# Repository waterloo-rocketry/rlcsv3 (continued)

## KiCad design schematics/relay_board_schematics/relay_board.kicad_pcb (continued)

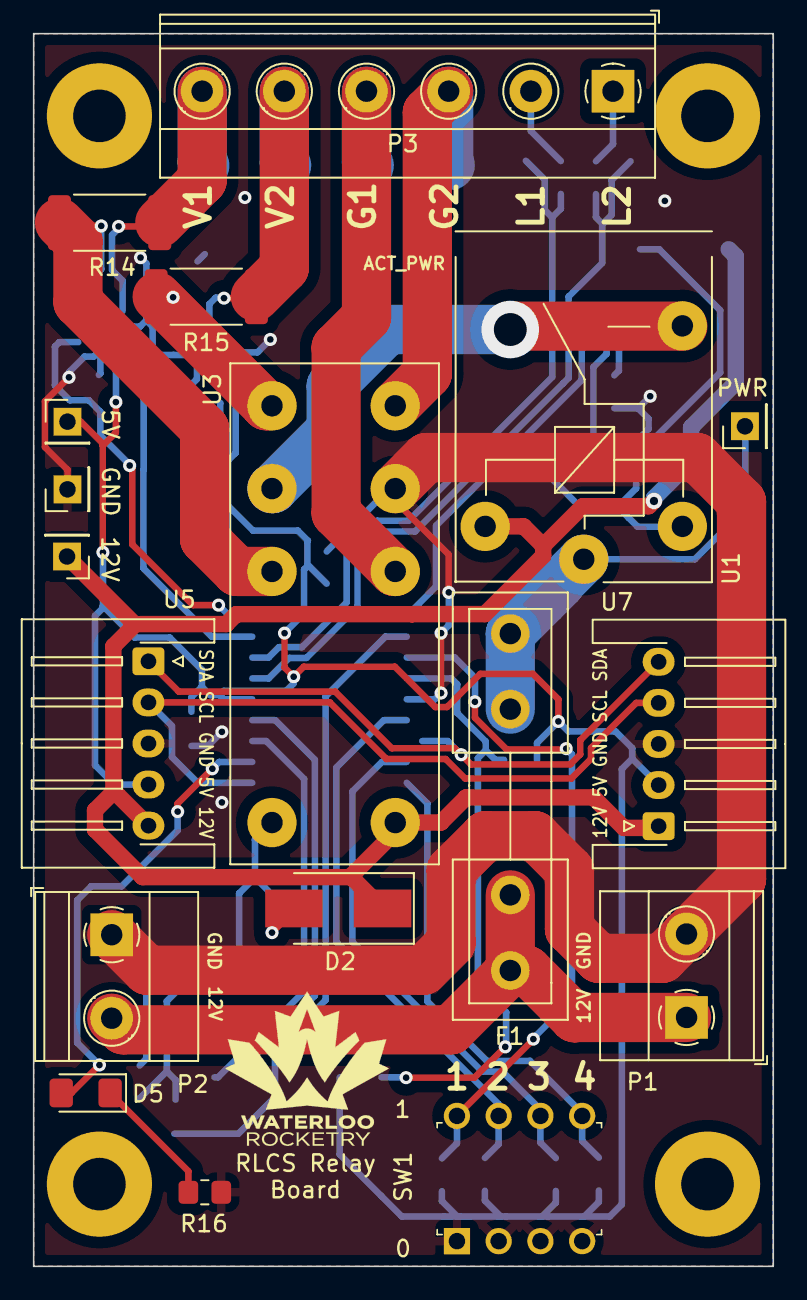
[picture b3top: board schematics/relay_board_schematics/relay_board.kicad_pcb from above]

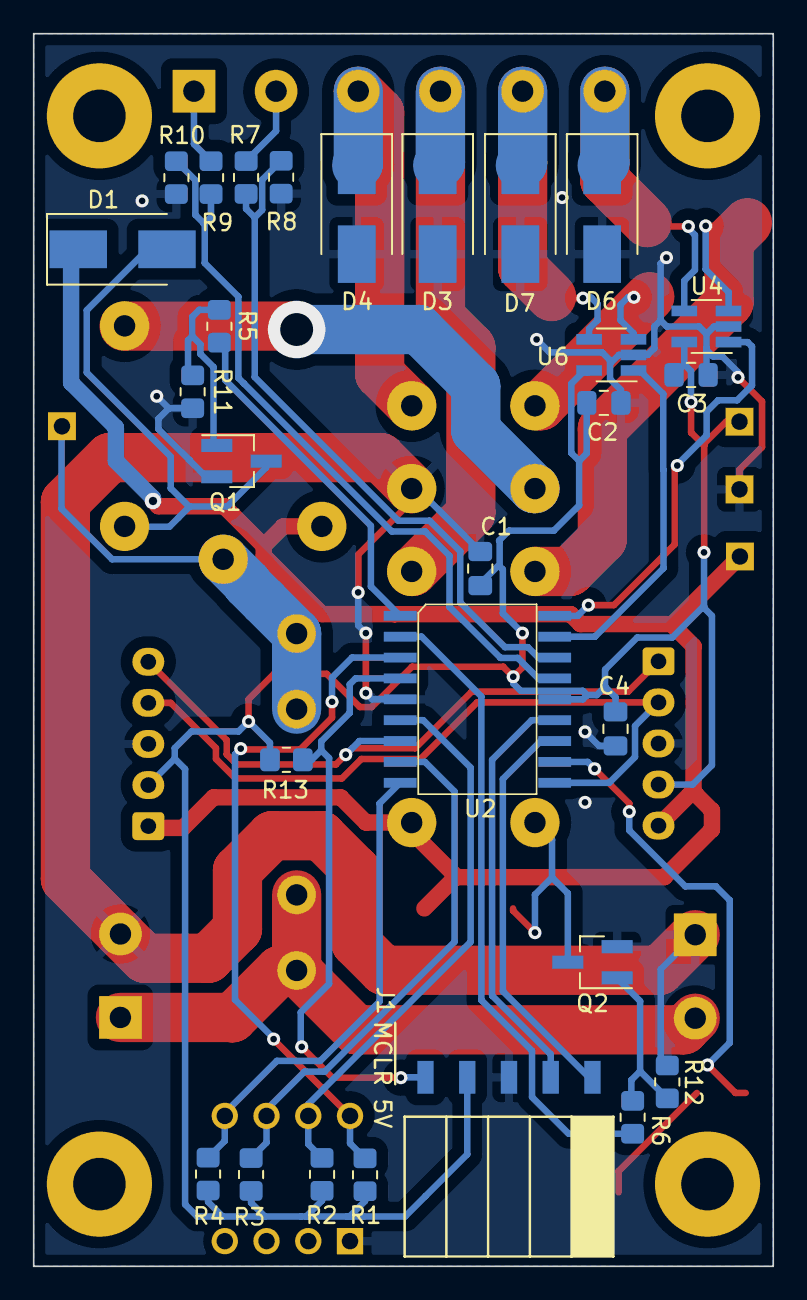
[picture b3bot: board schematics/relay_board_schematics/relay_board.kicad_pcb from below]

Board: 2 copper layers, 45.0 x 75.0 mm, 46 parts (28 on the bottom side), 35 nets.

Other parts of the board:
C4: 0.1uF; C_0805_2012Metric_Pad1.18x1.45mm_HandSolder

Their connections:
+5V: C4.2; also elsewhere on the board
GND: C4.1; also elsewhere on the board

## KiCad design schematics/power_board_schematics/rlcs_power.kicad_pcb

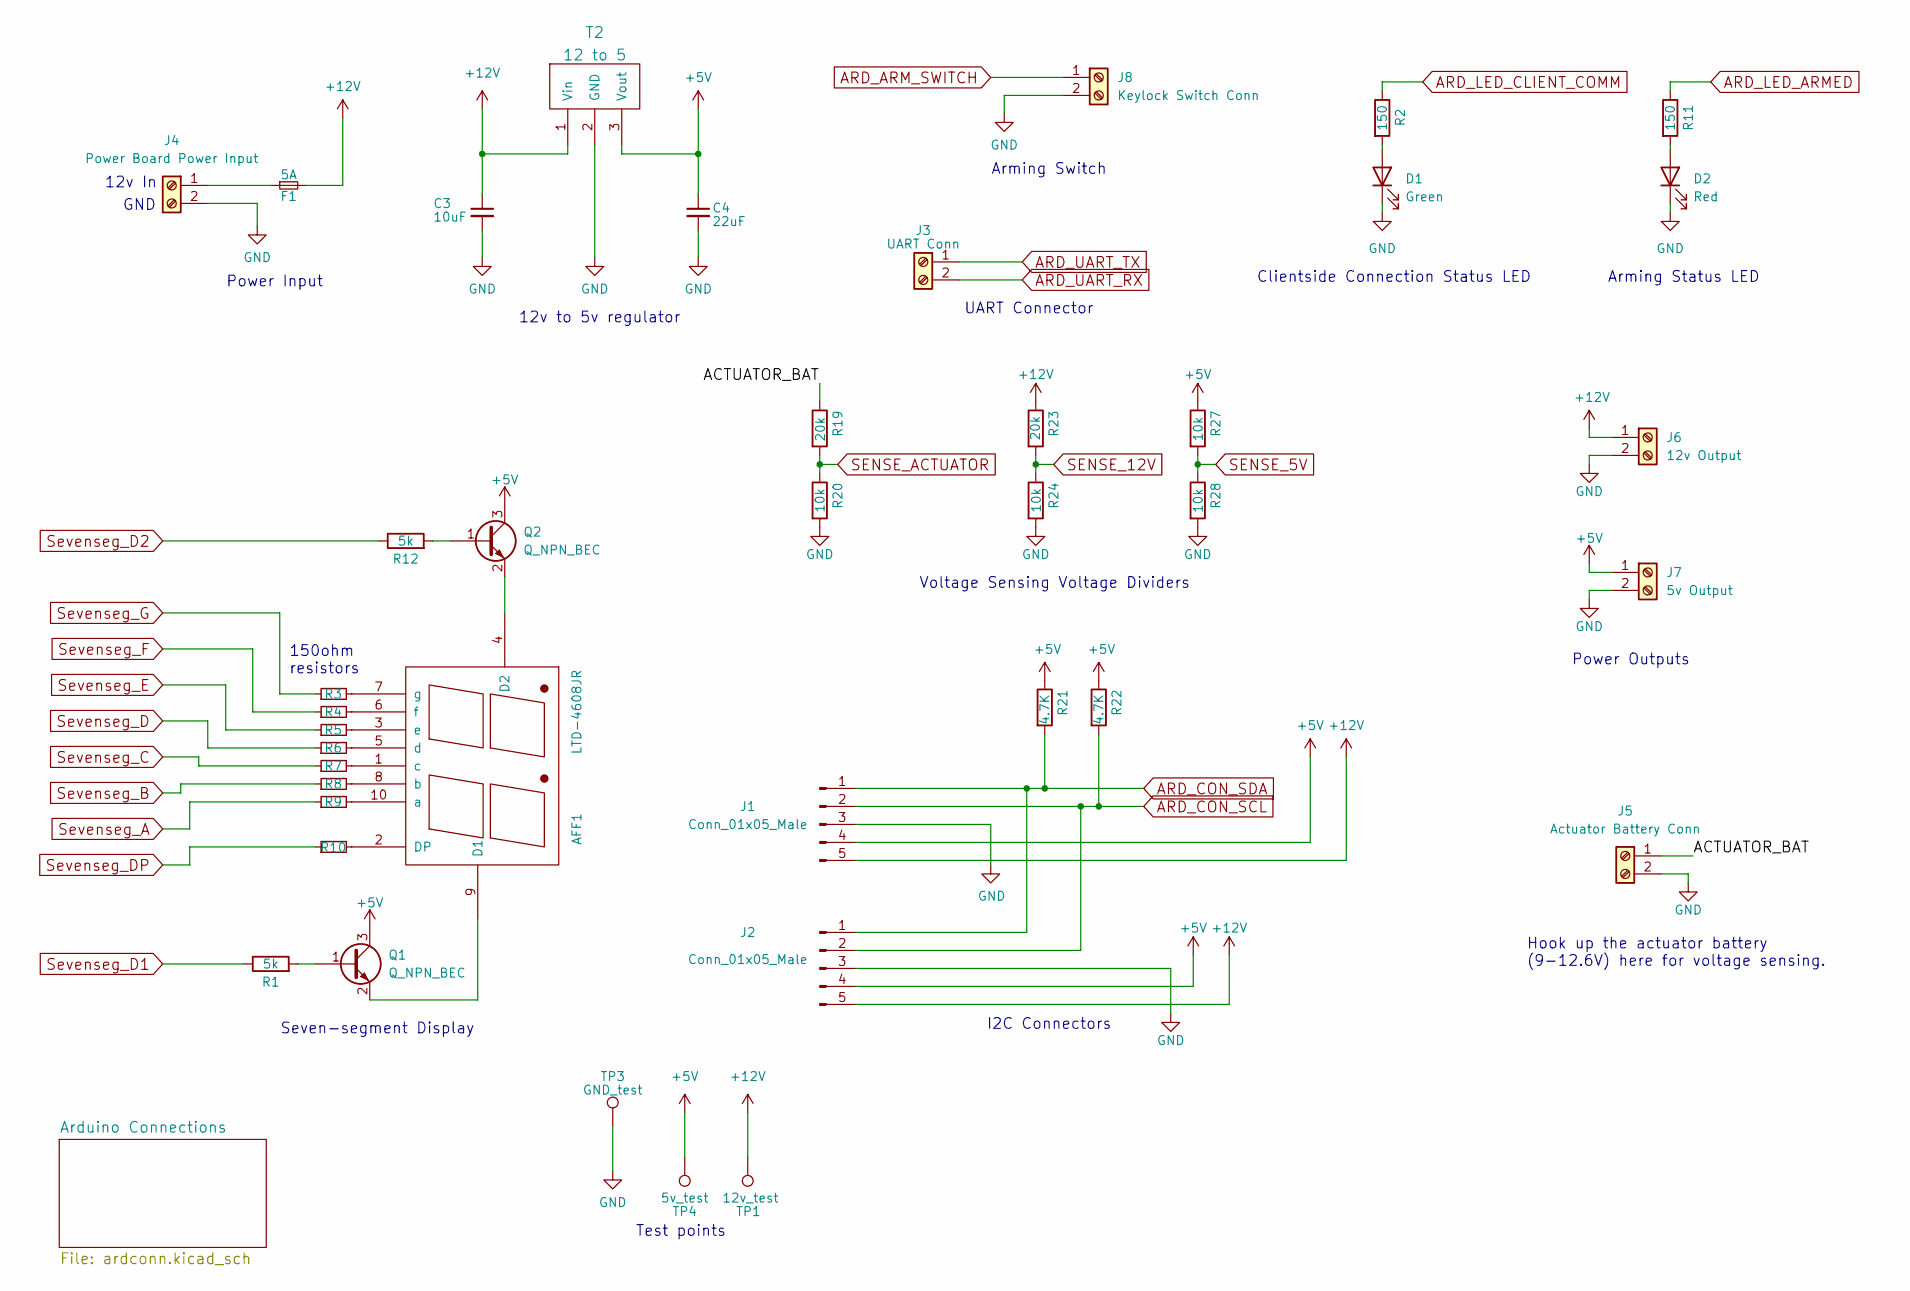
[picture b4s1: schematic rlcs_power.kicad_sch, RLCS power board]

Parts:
AFF1: LTD-4608JR
C3: 10uF; C_0805_2012Metric_Pad1.15x1.40mm_HandSolder
C4: 22uF; C_0805_2012Metric_Pad1.15x1.40mm_HandSolder
D1: Green; LED_1206_3216Metric_Pad1.42x1.75mm_HandSolder
D2: Red; LED_1206_3216Metric_Pad1.42x1.75mm_HandSolder
F1: 5A; Fuseholder5x20_horiz_open_inline_Type-I
J1, J2: Conn_01x05_Male; JST_EH_B5B-EH-A_1x05_P2.50mm_Vertical
J3: UART Conn; TerminalBlock_TE_282834-2_1x02_P2.54mm_Horizontal
J4: Power Board Power Input; TerminalBlock_Phoenix_MKDS-1,5-2-5.08_1x02_P5.08mm_Horizont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
J5: Actuator Battery Conn; TerminalBlock_Phoenix_MKDS-1,5-2-5.08_1x02_P5.08mm_Horizont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
J6: 12v Output; TerminalBlock_Phoenix_PT-1,5-2-5.0-H_1x02_P5.00mm_Horizontal
J7: 5v Output; TerminalBlock_Phoenix_PT-1,5-2-5.0-H_1x02_P5.00mm_Horizontal
J8: Keylock Switch Conn; TerminalBlock_TE_282834-2_1x02_P2.54mm_Horizontal
Q1, Q2: Q_NPN_BEC; SOT-523
R1, R12: 5k; R_0805_2012Metric_Pad1.20x1.40mm_HandSolder
R2, R3, R4, R5, R6, R7, R8, R9, R10, R11: 150; R_0805_2012Metric_Pad1.20x1.40mm_HandSolder
R19, R23: 20k; R_0805_2012Metric_Pad1.20x1.40mm_HandSolder
R20, R24, R27, R28: 10k; R_0805_2012Metric_Pad1.20x1.40mm_HandSolder
R21, R22: 4.7K; R_0805_2012Metric_Pad1.20x1.40mm_HandSolder
T2: 12 to 5; VXO78XX-1000
TP1: 12v_test; PinSocket_1x01_P2.00mm_Vertical
TP3: GND_test; PinSocket_1x01_P2.00mm_Vertical
TP4: 5v_test; PinSocket_1x01_P2.00mm_Vertical

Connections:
+5V: C4.1, J1.4, J2.4, J7.1, Q1.3 (C), Q2.3 (C), R21.1, R22.1, R27.1, T2.3 (Vout), TP4.1; also elsewhere on the board
+12V: C3.1, F1.2, J1.5, J2.5, J6.1, R23.1, T2.1 (Vin), TP1.1
/ACTUATOR_BAT: J5.1, R19.1
ARD_ARM_SWITCH: J8.1; also elsewhere on the board
ARD_CON_SCL: J1.2, J2.2, R22.2; also elsewhere on the board
ARD_CON_SDA: J1.1, J2.1, R21.2; also elsewhere on the board
ARD_LED_ARMED: R11.1; also elsewhere on the board
ARD_LED_CLIENT_COMM: R2.1; also elsewhere on the board
ARD_UART_RX: J3.2; also elsewhere on the board
ARD_UART_TX: J3.1; also elsewhere on the board
GND: C3.2, C4.2, D1.1 (K), D2.1 (K), J1.3, J2.3, J4.2, J5.2, J6.2, J7.2, J8.2, R20.2, R24.2, R28.2, T2.2 (GND), TP3.1; also elsewhere on the board
unnamed: AFF1.1 (c), R7.2
unnamed: AFF1.2 (DP), R10.2
unnamed: AFF1.3 (e), R5.2
unnamed: AFF1.4 (D2), Q2.2 (E)
unnamed: AFF1.5 (d), R6.2
unnamed: AFF1.6 (f), R4.2
unnamed: AFF1.7 (g), R3.2
unnamed: AFF1.8 (b), R8.2
unnamed: AFF1.9 (D1), Q1.2 (E)
unnamed: AFF1.10 (a), R9.2
unnamed: D1.2 (A), R2.2
unnamed: D2.2 (A), R11.2
unnamed: F1.1, J4.1
unnamed: Q1.1 (B), R1.2
unnamed: Q2.1 (B), R12.2
SENSE_5V: R27.2, R28.1; also elsewhere on the board
SENSE_12V: R23.2, R24.1; also elsewhere on the board
SENSE_ACTUATOR: R19.2, R20.1; also elsewhere on the board
Sevenseg_A: R9.1; also elsewhere on the board
Sevenseg_B: R8.1; also elsewhere on the board
Sevenseg_C: R7.1; also elsewhere on the board
Sevenseg_D: R6.1; also elsewhere on the board
Sevenseg_D1: R1.1; also elsewhere on the board
Sevenseg_D2: R12.1; also elsewhere on the board
Sevenseg_DP: R10.1; also elsewhere on the board
Sevenseg_E: R5.1; also elsewhere on the board
Sevenseg_F: R4.1; also elsewhere on the board
Sevenseg_G: R3.1; also elsewhere on the board

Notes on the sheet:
Hook up the actuator battery (9-12.6V) here for voltage sensing.
Arming Switch
UART Connector
12v In
GND
12v to 5v regulator
Clientside Connection Status LED
Voltage Sensing Voltage Dividers
Seven-segment Display
Power Input
Test points
I2C Connectors
Arming Status LED
150ohm resistors
Power Outputs

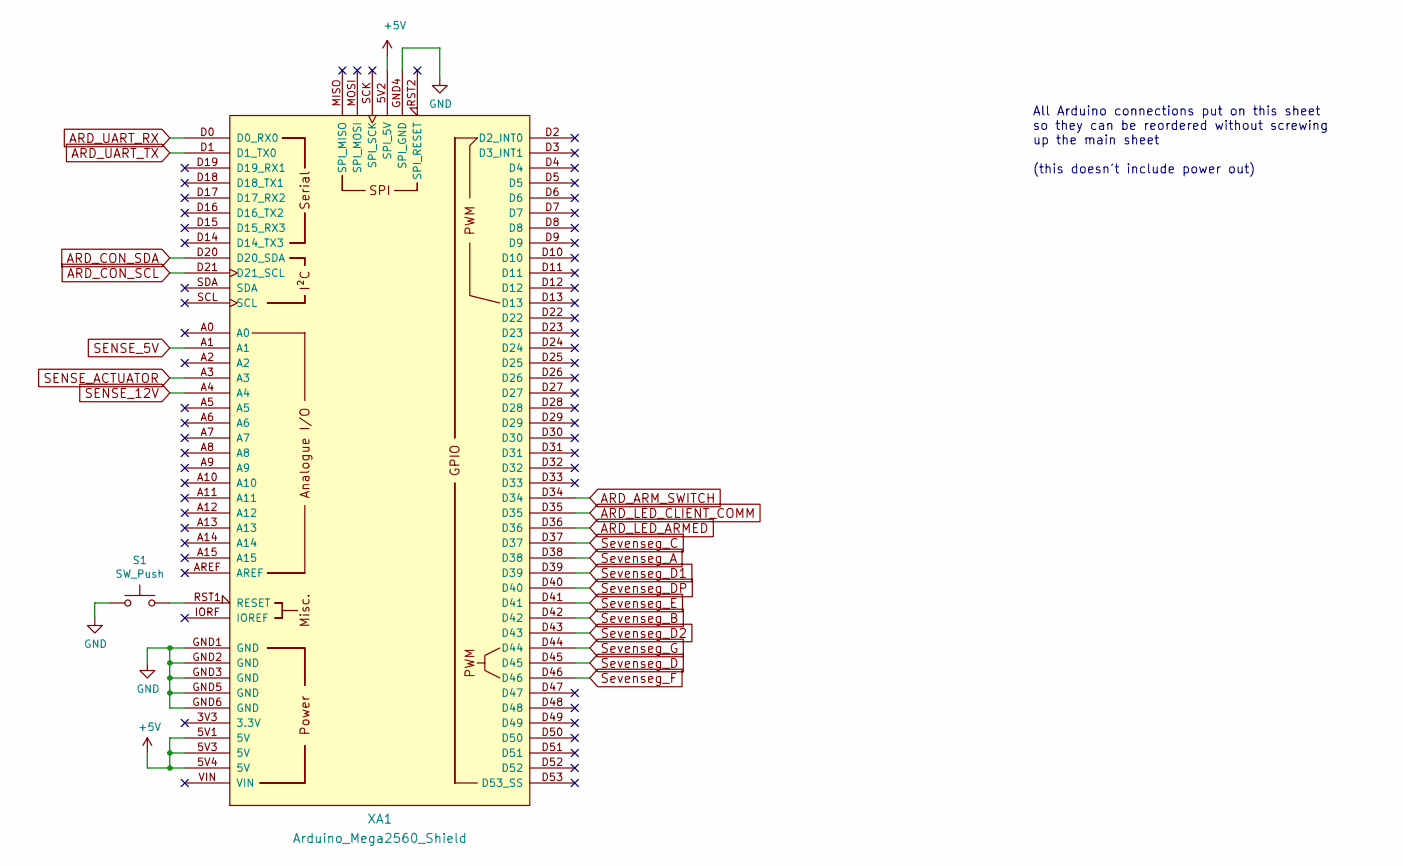
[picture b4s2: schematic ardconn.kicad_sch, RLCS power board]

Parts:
S1: SW_Push; SW_PUSH_6mm
XA1: Arduino_Mega2560_Shield

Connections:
+5V: XA1.5V1 (5V), XA1.5V2 (SPI_5V), XA1.5V3 (5V), XA1.5V4 (5V); also elsewhere on the board
ARD_ARM_SWITCH: XA1.D34; also elsewhere on the board
ARD_CON_SCL: XA1.D21 (D21_SCL); also elsewhere on the board
ARD_CON_SDA: XA1.D20 (D20_SDA); also elsewhere on the board
ARD_LED_ARMED: XA1.D36; also elsewhere on the board
ARD_LED_CLIENT_COMM: XA1.D35; also elsewhere on the board
ARD_UART_RX: XA1.D0 (D0_RX0); also elsewhere on the board
ARD_UART_TX: XA1.D1 (D1_TX0); also elsewhere on the board
GND: S1.1, XA1.GND1 (GND), XA1.GND2 (GND), XA1.GND3 (GND), XA1.GND4 (SPI_GND), XA1.GND5 (GND), XA1.GND6 (GND); also elsewhere on the board
unnamed: S1.2, XA1.RST1 (RESET)
SENSE_5V: XA1.A1; also elsewhere on the board
SENSE_12V: XA1.A4; also elsewhere on the board
SENSE_ACTUATOR: XA1.A3; also elsewhere on the board
Sevenseg_A: XA1.D38; also elsewhere on the board
Sevenseg_B: XA1.D42; also elsewhere on the board
Sevenseg_C: XA1.D37; also elsewhere on the board
Sevenseg_D: XA1.D45; also elsewhere on the board
Sevenseg_D1: XA1.D39; also elsewhere on the board
Sevenseg_D2: XA1.D43; also elsewhere on the board
Sevenseg_DP: XA1.D40; also elsewhere on the board
Sevenseg_E: XA1.D41; also elsewhere on the board
Sevenseg_F: XA1.D46; also elsewhere on the board
Sevenseg_G: XA1.D44; also elsewhere on the board

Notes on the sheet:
All Arduino connections put on this sheet so they can be reordered without screwing up the main sheet (this doesn't include power out)

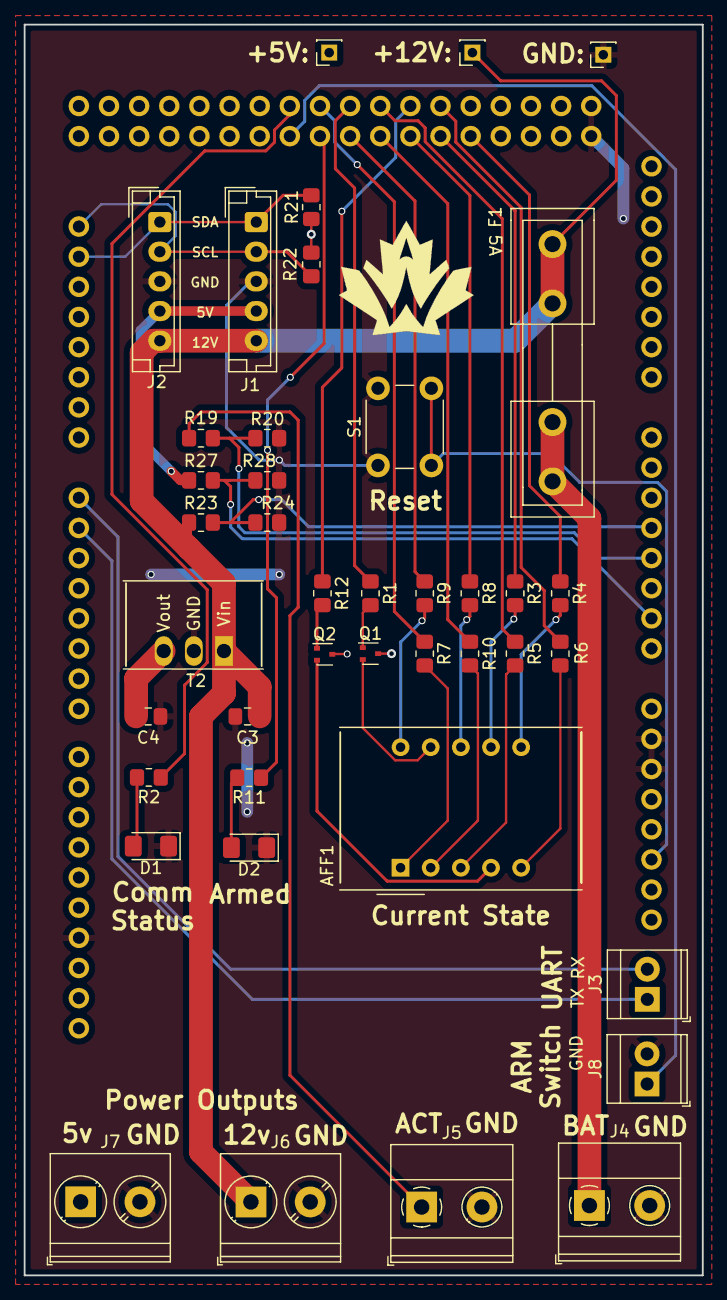
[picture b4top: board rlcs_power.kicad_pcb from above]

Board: 2 copper layers, 57.1 x 105.4 mm, 42 parts (0 on the bottom side), 40 nets.

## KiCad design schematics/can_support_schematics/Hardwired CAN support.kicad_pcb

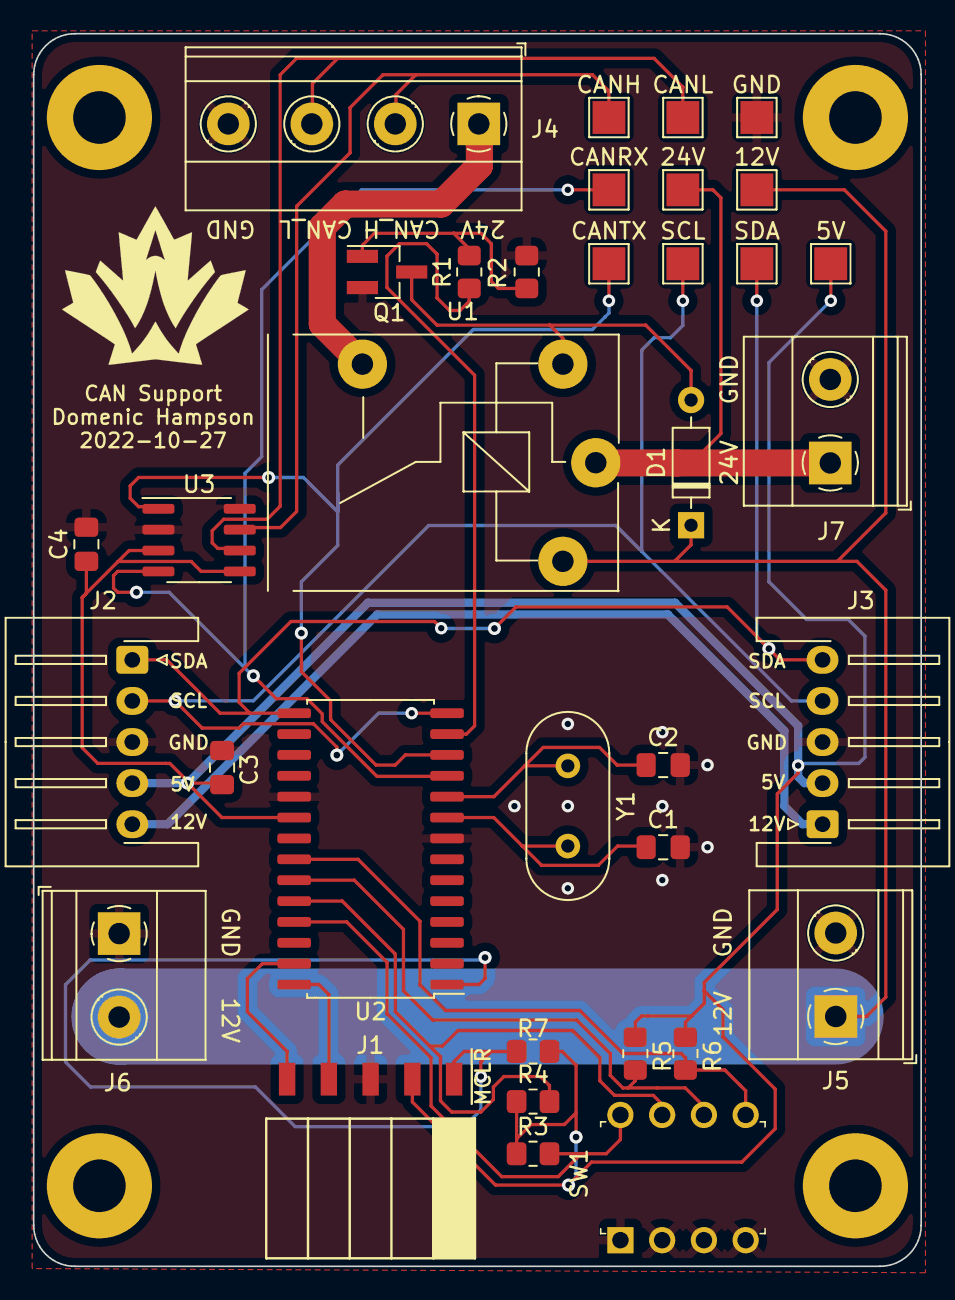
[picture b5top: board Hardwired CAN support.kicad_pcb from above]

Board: 2 copper layers, 54.0 x 75.0 mm, 35 parts (0 on the bottom side), 24 nets.

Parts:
5V, 12V, 24V: TestPoint; TestPoint_THTPad_2.0x2.0mm_Drill1.0mm
C1, C2: 27pF; C_0805_2012Metric_Pad1.18x1.45mm_HandSolder
C3: 0.1uF; C_0805_2012Metric_Pad1.18x1.45mm_HandSolder
C4: 10uF; C_0805_2012Metric_Pad1.18x1.45mm_HandSolder
CANH: TestPoint; TestPoint_THTPad_2.0x2.0mm_Drill1.0mm
CANL: TestPoint; TestPoint_THTPad_2.0x2.0mm_Drill1.0mm
CANRX: TestPoint; TestPoint_THTPad_2.0x2.0mm_Drill1.0mm
CANTX: TestPoint; TestPoint_THTPad_2.0x2.0mm_Drill1.0mm
D1: D; D_DO-35_SOD27_P7.62mm_Horizontal
GND: TestPoint; TestPoint_THTPad_2.0x2.0mm_Drill1.0mm
J1: Conn_01x05_Female; PinHeader_5x2.54_SMD_90deg_952-3198-1-ND
J2, J3: Conn_01x05_Male; JST_XH_S5B-XH-A-1_1x05_P2.50mm_Horizontal
J4: Screw_Terminal_01x04; TerminalBlock_Phoenix_MKDS-1,5-4-5.08_1x04_P5.08mm_Horizont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
J5, J6, J7: Screw_Terminal_01x02; TerminalBlock_Phoenix_MKDS-1,5-2-5.08_1x02_P5.08mm_Horizont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
Q1: MMBF170; SOT-23_Handsoldering
R1: 150R; R_0805_2012Metric_Pad1.20x1.40mm_HandSolder
R2: 10K; R_0805_2012Metric_Pad1.20x1.40mm_HandSolder
R3, R4, R5, R6, R7: 10k; R_0805_2012Metric_Pad1.20x1.40mm_HandSolder
SCL: TestPoint; TestPoint_THTPad_2.0x2.0mm_Drill1.0mm
SDA: TestPoint; TestPoint_THTPad_2.0x2.0mm_Drill1.0mm
SW1: SW_DIP_x04; DIP_SWITCH_4X2
U1: SPST_POWER_RELAY; Relay_SPST_G5LE-1A
U2: PIC18F26K83; SOIC-28W_7.5x17.9mm_P1.27mm
U3: MCP2562; SOIC-8_3.9x4.9mm_P1.27mm
Y1: Crystal; Crystal_HC49-4H_Vertical

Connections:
+5V: 5V.1, C3.1, C4.1, J1.2, J2.4, J3.2, R3.1, R4.1, R5.1, R6.1, R7.1, U2.20 (VDD), U3.3 (VDD), U3.5 (VIO)
+12V: 12V.1, D1.1 (K), J5.1, J6.2, U1.1 (CIN)
+24V: 24V.1, J7.1, U1.3 (SIN)
/BASE: Q1.1 (G), R1.2, R2.1
/CAN_H: CANH.1, J4.2, U3.7 (CANH)
/CAN_L: CANL.1, J4.3, U3.6 (CANL)
/CAN_RX: CANRX.1, U2.11 (RC0), U3.4 (RXD)
/CAN_TX: CANTX.1, U2.12 (RC1), U3.1 (TXD)
/DIP_1: R3.2, SW1.8, U2.25 (RB4)
/DIP_2: R4.2, SW1.7, U2.24 (RB3)
/DIP_3: R5.2, SW1.6, U2.23 (RB2)
/DIP_4: R6.2, SW1.5, U2.22 (RB1)
/DRAIN: D1.2 (A), Q1.3 (D), U1.2 (COUT)
/ICSPCLK: J1.5, U2.27 (RB6/ICSPCLK)
/ICSPDAT: J1.4, U2.28 (RB7/ICSPDAT)
/MCLR: J1.1, R7.2, U2.1 (~MCLR)
/OSC1: C1.1, U2.9 (RA7/OSC1), Y1.2
/OSC2: C2.1, U2.10 (RA6/OSC2), Y1.1
/RELAY_24V: J4.1, U1.4 (SOUT)
/SCL: J2.2, J3.4, SCL.1, U2.14 (RC3)
/SDA: J2.1, J3.5, SDA.1, U2.15 (RC4)
/TRIG_PIN: R1.1, U2.13 (RC2)
GND: C1.2, C2.2, C3.2, C4.2, GND.1, J1.3, J2.3, J3.3, J4.4, J5.2, J6.1, J7.2, Q1.2 (S), R2.2, SW1.1, SW1.2, SW1.3, SW1.4, U2.8 (VSS), U2.19 (VSS), U3.2 (VSS), U3.8 (STBY)
unnamed: J2.5, J3.1

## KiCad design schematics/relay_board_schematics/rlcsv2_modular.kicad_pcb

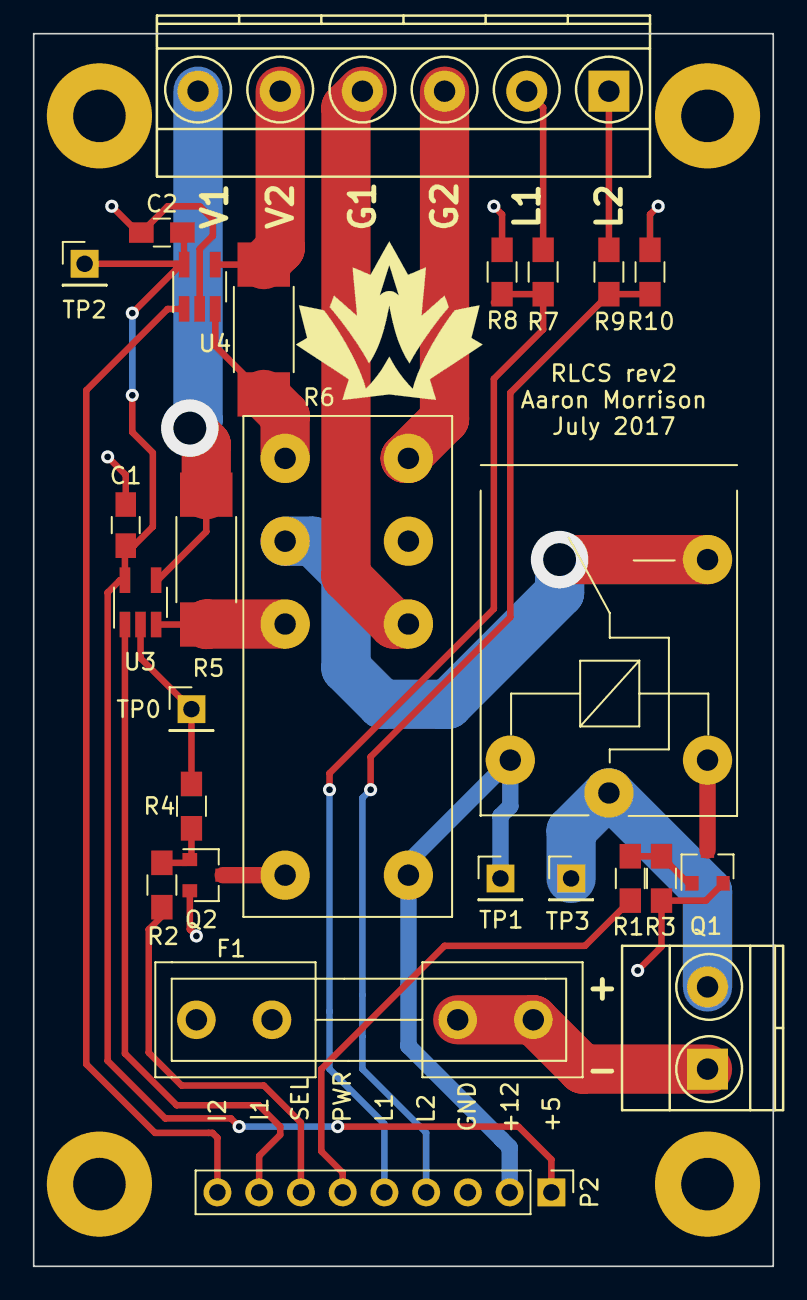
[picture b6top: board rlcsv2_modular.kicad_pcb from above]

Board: 2 copper layers, 45.0 x 75.0 mm, 26 parts (0 on the bottom side), 24 nets.

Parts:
C1, C2: 0.1uF; C_0805_HandSoldering
F1: FUSE; littlefuse_01000020Z
P1: ACT_PWR; TerminalBlock_Pheonix_MKDS1.5-2pol
P2: CONN_01X09; Socket_Strip_Straight_1x09_Pitch2.54mm
P3: ACTUATOR; TerminalBlock_Pheonix_MKDS1.5-6pol
Q1, Q2: MMBF170; SOT-23
R1, R2: 150; R_0805_HandSoldering
R3, R4, R8, R10: 10K; R_0805_HandSoldering
R5, R6: 0.02; R_2512_HandSoldering
R7, R9: 20K; R_0805_HandSoldering
TP0, TP1, TP2, TP3: TEST_1P; Socket_Strip_Straight_1x01_Pitch2.54mm
U1: SPST_POWER_RELAY; Relay_SPST_G5LE-1A
U2: dpdt_relay; Relay_DPDT_RT424012F
U3, U4: INA180A1; SOT-23-5_HandSoldering

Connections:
+5V: C1.2, C2.2, P2.1, TP2.1, U3.5, U4.5
+12V: P2.2, TP1.1, U1.1, U2.4
/Relays/G1: P3.4, U2.7
/Relays/G2: P3.3, U2.8
/Relays/P1: P3.6, R5.1, U3.4
/Relays/P2: P3.5, R6.1, U4.4
/Relays/VIN: P1.2, TP3.1, U1.3
CS_1: P2.8, U3.1
CS_2: P2.9, U4.1
GND: C1.1, C2.1, F1.2, P2.3, Q1.2, Q2.2, R3.2, R4.2, R8.2, R10.2, TP0.1, U2.2, U3.2, U4.2
LIM1: P2.5, R7.2, R8.1
LIM2: P2.4, R9.2, R10.1
unnamed: F1.1, P1.1
unnamed: P3.1, R9.1
unnamed: P3.2, R7.1
unnamed: Q1.1, R1.1, R3.1
unnamed: Q1.3, U1.2
unnamed: Q2.1, R2.1, R4.1
unnamed: Q2.3, U2.3
unnamed: R5.2, U2.5, U3.3
unnamed: R6.2, U2.6, U4.3
unnamed: U1.4, U2.1
POWER: P2.6, R1.2
SELECT: P2.7, R2.2

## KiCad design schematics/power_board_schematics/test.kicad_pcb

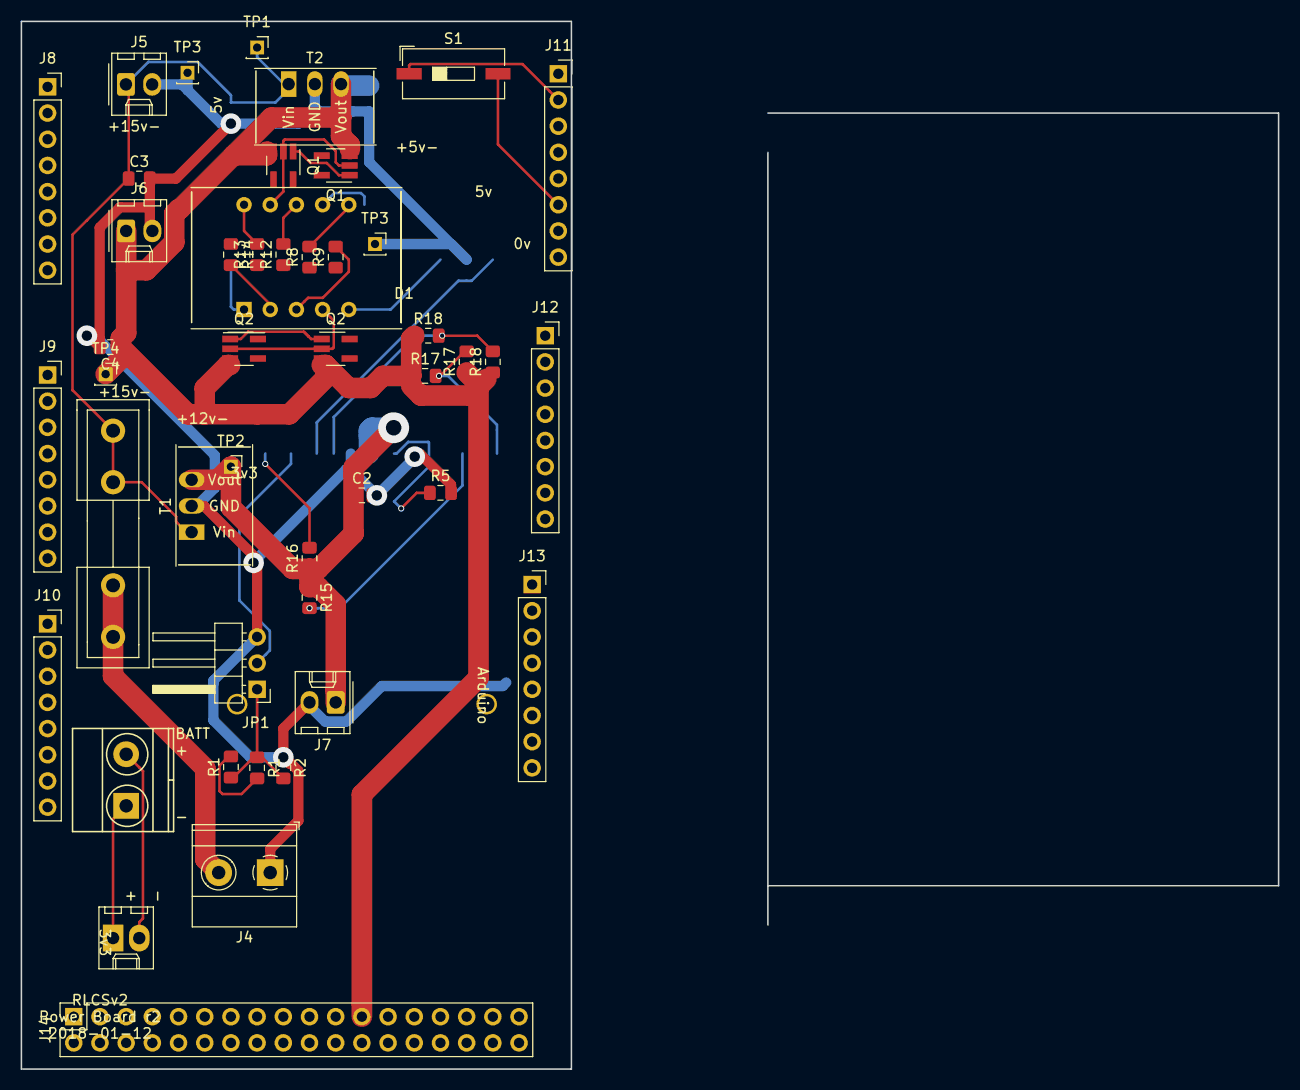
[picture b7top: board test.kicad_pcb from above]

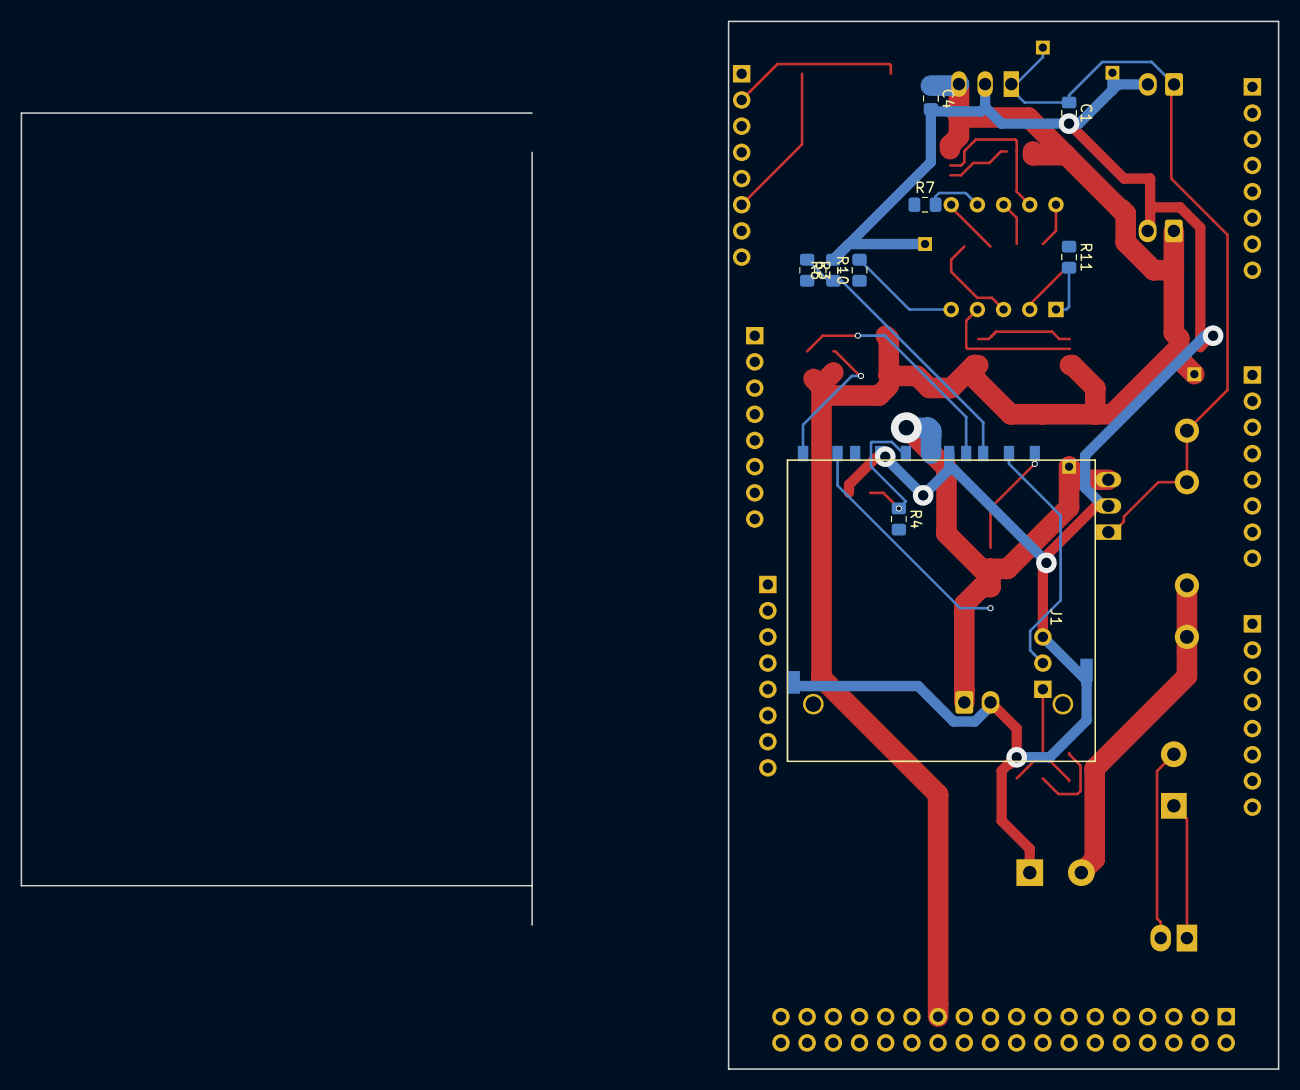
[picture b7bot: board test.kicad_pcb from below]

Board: 2 copper layers, 121.9 x 101.6 mm, 55 parts (9 on the bottom side), 30 nets.

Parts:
AFF1: LTD-4608JR
C1, C3: 10uF; C_0805_2012Metric_Pad1.15x1.40mm_HandSolder
C2, C4, C4#2: 22uF; C_0805_2012Metric_Pad1.15x1.40mm_HandSolder
F1: Fuse_Small; Fuseholder5x20_horiz_open_inline_Type-I
J1: SD_Card; SDCARD
J2: Conn_01x05_Male; TerminalBlock_Pheonix_MKDS1.5-2pol
J3: Conn_01x05_Male; Molex_KK-6410-02_02x2.54mm_Straight
J4: Battery Conn; TerminalBlock_Phoenix_MKDS-1,5-2_1x02_P5.00mm_Horizontal
J5, J6, J7: CONN_01X02; Molex_KK-254_AE-6410-02A_1x02_P2.54mm_Vertical
J8: Conn_0_to_7; PinSocket_1x08_P2.54mm_Vertical
J9: conn_8_to_13; PinSocket_1x08_P2.54mm_Vertical
J10: Conn_14_to_21; PinSocket_1x08_P2.54mm_Vertical
J11: conn_power; PinSocket_1x08_P2.54mm_Vertical
J12: conn_A8_to_A15; PinSocket_1x08_P2.54mm_Vertical
J13: conn_A0_to_A7; PinSocket_1x08_P2.54mm_Vertical
J14: conn_22_to_53; PinSocket_2x18_P2.54mm_Vertical
JP1: Jumper_NC_Dual; PinHeader_1x03_P2.54mm_Horizontal
Q1, Q1#2, Q2, Q2#2: Q_NPN_BEC; SOT-23-5_HandSoldering
R1, R1#2, R5, R6, R15, R16: 20K; R_0805_2012Metric_Pad1.15x1.40mm_HandSolder
R2, R3, R4, R17, R17#2, R18, R18#2: 10K; R_0805_2012Metric_Pad1.15x1.40mm_HandSolder
R7, R8, R9, R10, R11, R12, R13, R14: 150; R_0805_2012Metric_Pad1.15x1.40mm_HandSolder
S1: SW_Push; SW_DIP_SPSTx01_Slide_9.78x4.72mm_W8.61mm_P2.54mm
T1: 12 to 3v3; VXO78XX-1000
T2: 12 to 5; VXO78XX-1000
TP1: 12v_test; PinSocket_1x01_P2.00mm_Vertical
TP2: 3v3_test; PinSocket_1x01_P2.00mm_Vertical
TP3, TP3#2: GND_test; PinSocket_1x01_P2.00mm_Vertical
TP4: 5v_test; PinSocket_1x01_P2.00mm_Vertical

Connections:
+3V3: C2.1, J1.4, J7.1, R15.1, R16.1, T1.3, TP2.1
+5V: C4.1, C4#2.1, J6.1, J14.22, J14.23, Q1.3, Q1#2.3, Q2.3, Q2#2.3, R17.1, R17#2.1, R18.1, R18#2.1, T2.3, TP4.1
+12V: C1.1, C3.1, F1.2, J5.1, T1.1, T2.1, TP1.1
/SCL: J2.2, J3.2
/SDA: J2.1, J3.1
ARD_CON_7SEG_D1: Q2.1, Q2#2.1
ARD_CON_7SEG_D2: Q1.1, Q1#2.1
ARD_CON_SD_CD: J1.10, R18.2, R18#2.2
ARD_CON_SD_SS: R1.2, R1#2.2
ARD_CON_SD_WP: J1.11, R17.2, R17#2.2
GND: C1.2, C2.2, C3.2, C4.2, C4#2.2, J1.3, J1.6, J1.12, J1.13, J4.1, J5.2, J6.2, J7.2, JP1.3, R2.1, R5.2, R6.2, T1.2, T2.2, TP3.1, TP3#2.1
unnamed: AFF1.1, R11.2
unnamed: AFF1.2, R14.2
unnamed: AFF1.3, R9.2
unnamed: AFF1.4, Q2.2, Q2#2.2
unnamed: AFF1.5, R10.2
unnamed: AFF1.6, R8.2
unnamed: AFF1.7, R7.2
unnamed: AFF1.8, R12.2
unnamed: AFF1.9, Q1.2, Q1#2.2
unnamed: AFF1.10, R13.2
unnamed: F1.1, J4.2
unnamed: J1.1, JP1.2
unnamed: J1.2, R3.1, R6.1
unnamed: J1.5, R4.1, R5.1
unnamed: J1.8, R15.2
unnamed: J1.9, R16.2
unnamed: J11.2, S1.1
unnamed: J11.6, S1.2
unnamed: JP1.1, R1.1, R1#2.1, R2.2

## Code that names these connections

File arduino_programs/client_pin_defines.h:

#ifndef CLIENT_PIN_DEFINES_H
#define CLIENT_PIN_DEFINES_H

//pins for the switches
#define PIN_SWITCH_REMOTEFILL    33
#define PIN_SWITCH_REMOTEVENT    37
#define PIN_SWITCH_ROCKETVALVE   35
#define PIN_SWITCH_LINACTUATOR   36
#define PIN_SWITCH_INJECTOR      34
#define PIN_SWITCH_IGNITION_PRI  32
#define PIN_SWITCH_IGNITION_SEC  31
#define PIN_SWITCH_IGNITION_FIRE 30

//pins for the LCD output
#define PIN_LCD_RS 25
#define PIN_LCD_EN 24
#define PIN_LCD_D4 29
#define PIN_LCD_D5 27
#define PIN_LCD_D6 28
#define PIN_LCD_D7 26

//pins for the status LEDs
#define PIN_LED_GREEN 23
#define PIN_LED_RED   22

//pins for the seven segment display
#define PIN_SEVENSEG_D1 47
#define PIN_SEVENSEG_D2 46
#define PIN_SEVENSEG_A  39
#define PIN_SEVENSEG_B  40
#define PIN_SEVENSEG_C  42
#define PIN_SEVENSEG_D  44
#define PIN_SEVENSEG_E  43
#define PIN_SEVENSEG_F  41
#define PIN_SEVENSEG_G  38
#define PIN_SEVENSEG_DP 45

//pins for the SD card
#define PIN_SD_SS 53

#endif //ifndef CLIENT_PIN_DEFINES_H

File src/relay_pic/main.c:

#include <stdint.h>
#include <stdlib.h>
#include <xc.h>
#include "i2c.h"
#include "relay_general.h"
#include "timer.h"

#define MAX_LOOP_TIME_DIFF_CONST 500

uint16_t dip_inputs;

static void __interrupt() interrupt_handler(void) {
    //We received a i2c request from master, handle it.
    if (SSP1IF == 1) {
       i2c_handle_interrupt();
    }
    // Timer0 has overflowed - update millis() function
    // This happens approximately every 500us
    if (INTCONbits.TMR0IE == 1 && INTCONbits.TMR0IF == 1) {
        timer0_handle_interrupt();
        INTCONbits.TMR0IF = 0;
    }
}

void read_dip_inputs(void) {
    uint16_t new_dip = 0;
    new_dip |= (!PORTBbits.RB3) ? (1) : 0;       //LSB
    new_dip |= (!PORTBbits.RB2) ? (1 << 1) : 0;
    new_dip |= (!PORTBbits.RB0) ? (1 << 2) : 0;
    new_dip |= (!PORTAbits.RA4) ? (1 << 3) : 0;  //MSB
    if(dip_inputs != new_dip) {
        dip_inputs = new_dip;
        i2c_slave_init(dip_inputs); //reinitialize i2c slave module with new slave address
    }
}

void setup(void) {
    OSCCONbits.IRCF = 0b1101; // Set internal oscillator clock speed to 4 mhz (default is 500k)
    
    TRISAbits.TRISA0 = 1;   //CURR_SENSE_2
    TRISAbits.TRISA1 = 1;   //CURR_SENSE_1
    TRISAbits.TRISA2 = 0;   //POWER
    TRISAbits.TRISA3 = 0;   //SELECT
    TRISAbits.TRISA4 = 1;   //DIP_1
    TRISAbits.TRISA6 = 1;   //LIM2
    TRISAbits.TRISA7 = 1;   //LIM1
    TRISBbits.TRISB0 = 1;   //DIP_2
    TRISBbits.TRISB2 = 1;   //DIP_3
    TRISBbits.TRISB3 = 1;   //DIP_4
    TRISBbits.TRISB5 = 0;   //LED

    ANSELA = 0;             //DISABLE ANALOG INPUT ON PORT A, then enable port 0 and 1
    ANSELAbits.ANSA0 = 1;   //CURR_SENSE_2
    ANSELAbits.ANSA1 = 1;   //CURR_SENSE_1

    ANSELB = 0;             //DISABLE ANALOG INPUT ON PORT B

    // Configure FVR module
    // b[7] enables FVR
    // b[1:0] sets the reference to 4.096
    FVRCON = 0b10000011;

    // Configure ADC module
    // b[7] sets right justification, b[6:4] sets CS = FRC,
    // b[2]+b[1:0] sets Vss and FVR as references.
    ADCON1 = 0b11110011;
}

int main(int argc, char** argv) {
    setup();                    //Set up digital + analog I/O
    timer0_init();              //Initialize timer
    set_power_on();
    set_select_off();
    set_led_off();
    dip_inputs = 0;
    i2c_slave_init(dip_inputs);
    read_dip_inputs();            //Get actual dip switch value to set slave address, init i2c

    uint32_t last_millis = millis();

    while (1) {
        //Heartbeat
        if (millis() - last_millis > MAX_LOOP_TIME_DIFF_CONST) {
            //One day I will configure this correctly, but ATM we only need the LED to blink ;-;
            last_millis = millis();

            led_heartbeat();
        }

        read_analog_inputs(CURR_SENSE_1);
        read_analog_inputs(CURR_SENSE_2);

        read_dip_inputs(); //Check if dip switch input has changed, re-init i2c if so
    }
    return (EXIT_SUCCESS);
}
